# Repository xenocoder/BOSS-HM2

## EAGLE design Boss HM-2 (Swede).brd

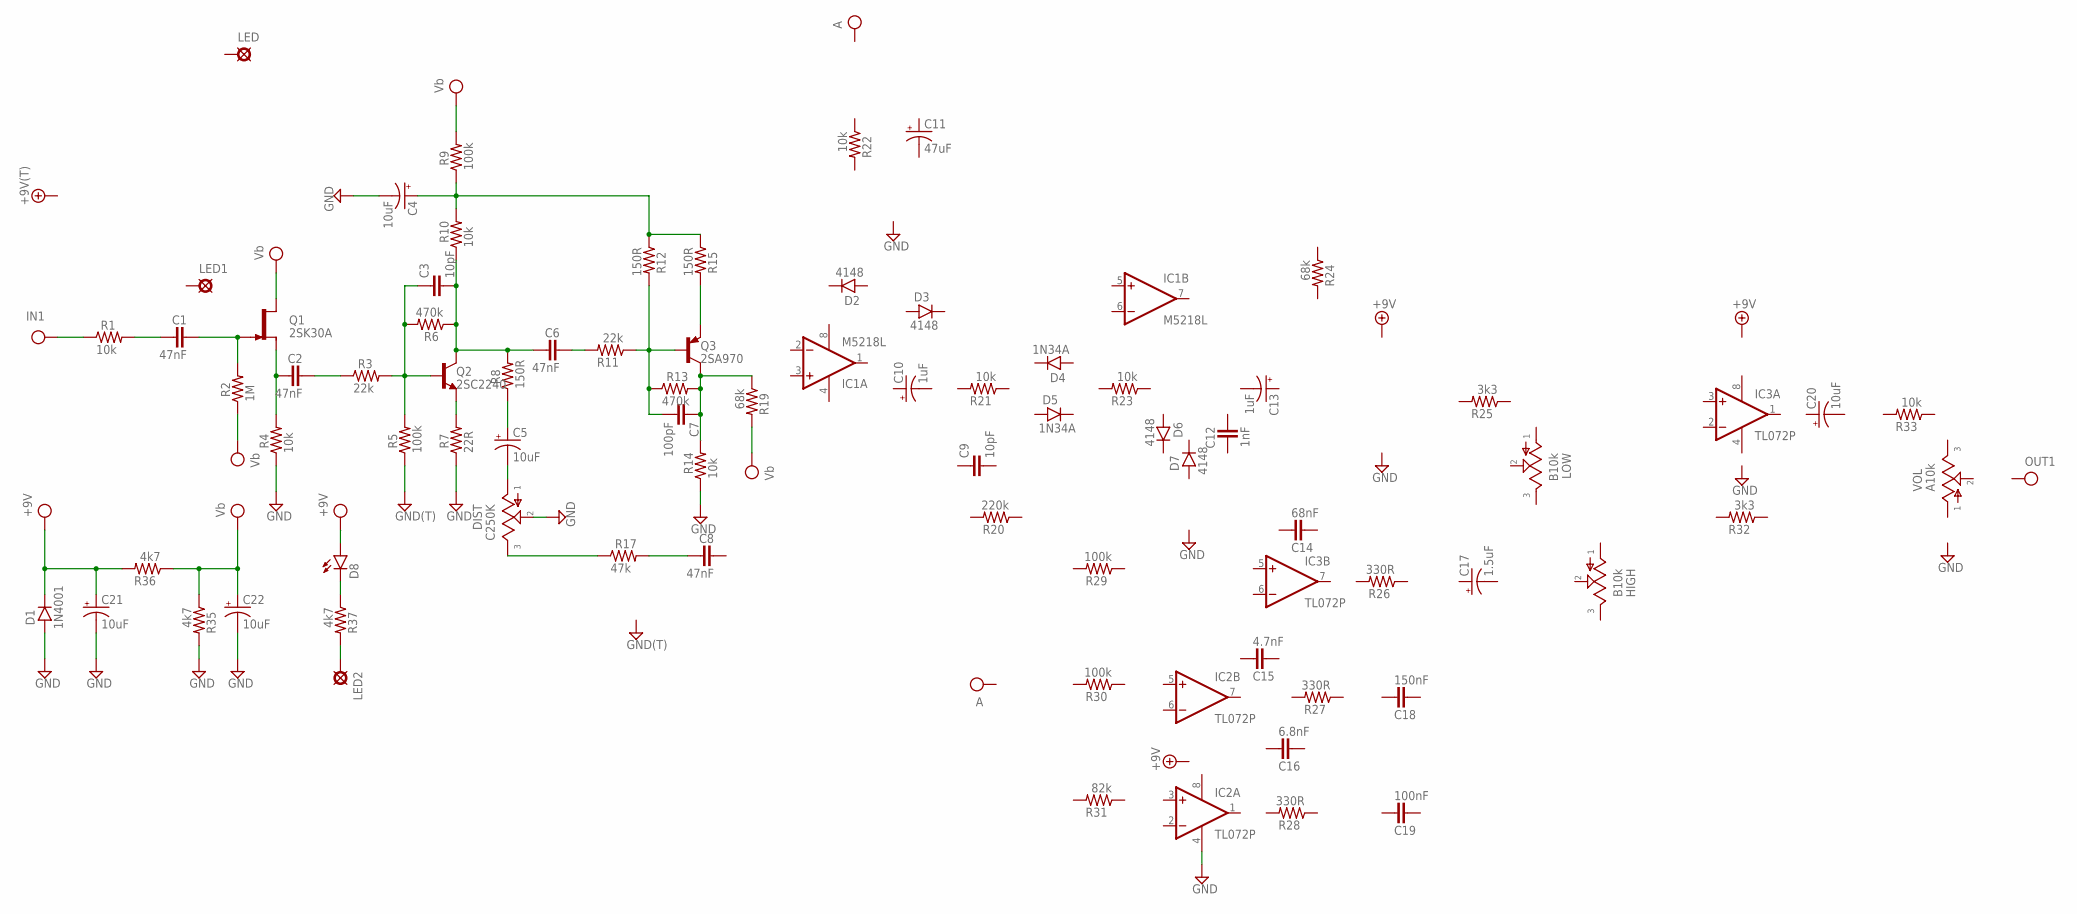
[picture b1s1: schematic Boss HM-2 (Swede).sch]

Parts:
+9V1: +9V(T); SQUARE
C1, C2, C6, C8: 47nF; 072X025
C3, C9: 10pF; 050X030_025
C4, C5, C20, C21, C22: 10uF; 050_020_1
C7: 100pF; 050X030_025
C10, C13: 1uF; 050_020_1
C11: 47uF; 050_020_1
C12: 1nF; 072X025
C14: 68nF; 072X025
C15: 4.7nF; 072X025
C16: 6.8nF; 072X025
C17: 1.5uF; 050_020_1
C18: 150nF; 072X025
C19: 100nF; 072X025
D1: 1N4001; DO35-3
D2, D3, D6, D7: 4148; DO35-3
D4, D5: 1N34A; DO07
D8: LED3MM
DIST: C250K; 16MM_PCB_PADS
GND1, GND2: GND(T); SQUARE
HIGH: B10k; 16MM_PCB_PADS
IC1: M5218L; DIL08
IC2, IC3: TL072P; DIL08
IN1: IN(T); SQUARE
LED, LED1, LED2: PAD; SQUARE
LOW: B10k; 16MM_PCB_PADS
OUT1: OUT(T); SQUARE
Q1: 2SK30A; TO92-
Q2: 2SC2240; TO92-
Q3: 2SA970; TO92-
R1, R4, R10, R14, R21, R22, R23, R33: 10k; R0207/3
R2: 1M; R0207/3
R3, R11: 22k; R0207/3
R5, R9, R29, R30: 100k; R0207/3
R6, R13: 470k; R0207/3
R7: 22R; R0207/3
R8, R12, R15: 150R; R0207/3
R17: 47k; R0207/3
R19, R24: 68k; R0207/3
R20: 220k; R0207/3
R25, R32: 3k3; R0207/3
R26, R27, R28: 330R; R0207/3
R31: 82k; R0207/3
R35, R36, R37: 4k7; R0207/3
VOL: A10k; 16MM_PCB_PADS

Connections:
A: C21.+, C22.+, D1.C, D8.A, Q1.3 (D), R2.1, R9.2, R19.2, R35.1, R36.1, R36.2
GND: C4.-, C21.-, C22.-, D1.A, DIST.2, GND1.1, IC2.4 (V-), R4.1, R5.1, R7.1, R14.1, R35.2
IN: IN1.1, R1.1
unnamed: D8.K (C), R37.1
unnamed: C1.1, R1.2
unnamed: C1.2, Q1.2 (G), R2.2
unnamed: C2.1, Q1.1 (S), R4.2
unnamed: C2.2, R3.1
unnamed: C3.1, Q2.2 (B), R3.2, R5.2, R6.2
unnamed: Q2.3 (E), R7.2
unnamed: C3.2, C6.1, Q2.1 (C), R6.1, R8.2, R10.1
unnamed: C5.+, R8.1
unnamed: C5.-, DIST.1
unnamed: LED2.1, R37.2
unnamed: C4.+, R9.1, R10.2, R12.1, R15.1
unnamed: C6.2, R11.2
unnamed: C7.2, Q3.1 (B), R11.1, R12.2, R13.1
unnamed: C7.1, Q3.2 (C), R13.2, R14.2, R19.1
unnamed: DIST.3, R17.1
unnamed: C8.1, R17.2
unnamed: Q3.3 (E), R15.2
V+: IC1.8 (V+), IC2.8 (V+), IC3.8 (V+)
V-: IC1.4 (V-), IC3.4 (V-)

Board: 2 copper layers, 82 parts (0 on the bottom side), 23 nets, no tracks yet.

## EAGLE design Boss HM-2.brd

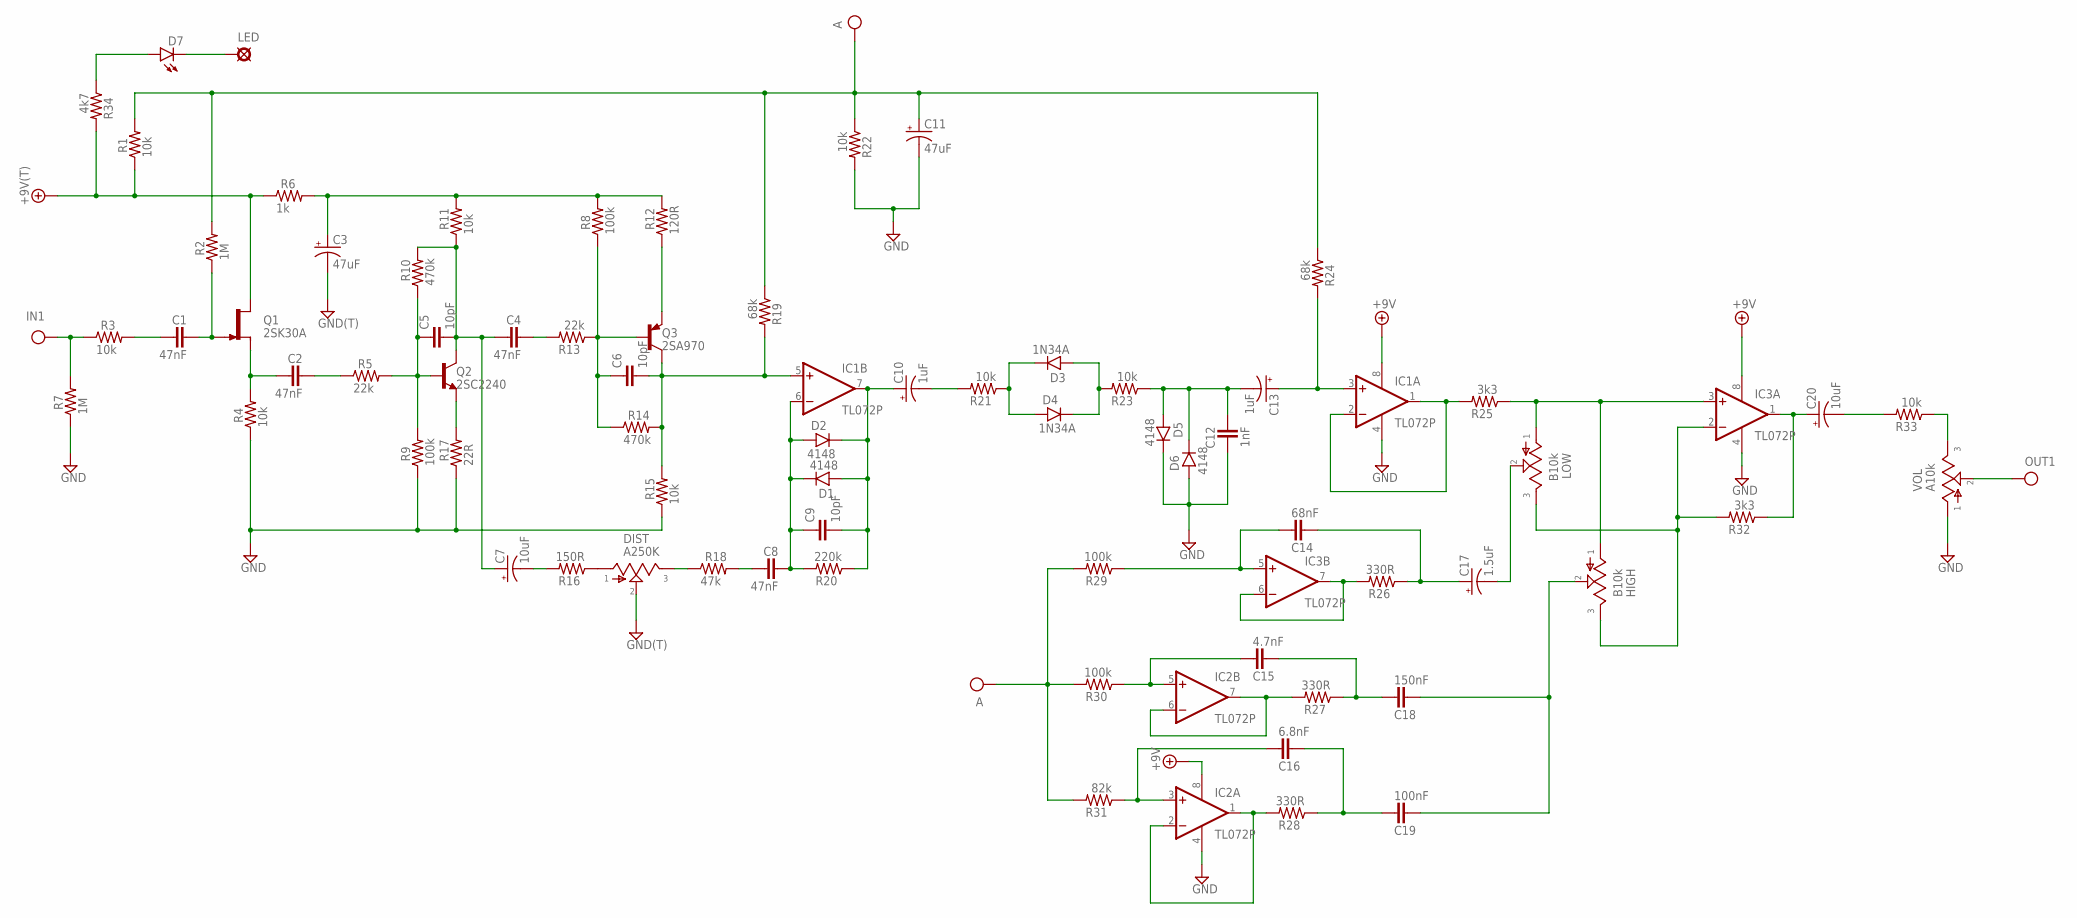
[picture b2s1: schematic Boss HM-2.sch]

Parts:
+9V1: +9V(T); SQUARE
C1, C2, C4, C8: 47nF; 072X025
C3, C11: 47uF; 050_020_1
C5, C6, C9: 10pF; 050X030_025
C7, C20: 10uF; 050_020_1
C10, C13: 1uF; 050_020_1
C12: 1nF; 072X025
C14: 68nF; 072X025
C15: 4.7nF; 072X025
C16: 6.8nF; 072X025
C17: 1.5uF; 050_020_1
C18: 150nF; 072X025
C19: 100nF; 072X025
D1, D2, D5, D6: 4148; DO35-3
D3, D4: 1N34A; DO07
D7: LED3MM
DIST: A250K; 16MM_PCB_PADS
GND1, GND2: GND(T); SQUARE
HIGH: B10k; 16MM_PCB_PADS
IC1, IC2, IC3: TL072P; DIL08
IN1: IN(T); SQUARE
LED: PAD; SQUARE
LOW: B10k; 16MM_PCB_PADS
OUT1: OUT(T); SQUARE
Q1: 2SK30A; TO92-
Q2: 2SC2240; TO92-
Q3: 2SA970; TO92-
R1, R3, R4, R11, R15, R21, R22, R23, R33: 10k; R0207/3
R2, R7: 1M; R0207/3
R5, R13: 22k; R0207/3
R6: 1k; R0207/3
R8, R9, R29, R30: 100k; R0207/3
R10, R14: 470k; R0207/3
R12: 120R; R0207/3
R16: 150R; R0207/3
R17: 22R; R0207/3
R18: 47k; R0207/3
R19, R24: 68k; R0207/3
R20: 220k; R0207/3
R25, R32: 3k3; R0207/3
R26, R27, R28: 330R; R0207/3
R31: 82k; R0207/3
R34: 4k7; R0207/3
VOL: A10k; 16MM_PCB_PADS

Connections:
+9V: +9V1.1, IC1.8 (V+), IC2.8 (V+), IC3.8 (V+), Q1.3 (D), R1.1, R6.1, R34.2
A: C11.+, R1.2, R2.2, R19.1, R22.1, R24.1, R29.2, R30.2, R31.2
GND: C3.-, C11.-, C12.1, D5.C, D6.A, DIST.2, GND1.1, GND2.1, IC1.4 (V-), IC2.4 (V-), IC3.4 (V-), R4.1, R7.1, R9.1, R15.1, R17.1, R22.2, VOL.1
IN: IN1.1, R3.1, R7.2
unnamed: C1.1, R3.2
unnamed: C5.1, Q2.2 (B), R5.2, R9.2, R10.1
unnamed: C1.2, Q1.2 (G), R2.1
unnamed: C3.+, R6.2, R8.2, R11.2, R12.2
unnamed: C2.1, Q1.1 (S), R4.2
unnamed: C2.2, R5.1
unnamed: C4.1, C5.2, C7.+, Q2.1 (C), R10.2, R11.1
unnamed: Q2.3 (E), R17.2
unnamed: C4.2, R13.2
unnamed: C7.-, R16.2
unnamed: C6.1, Q3.1 (B), R8.1, R13.1, R14.1
unnamed: C6.2, IC1.5 (+IN), Q3.2 (C), R14.2, R15.2, R19.2
unnamed: Q3.3 (E), R12.1
unnamed: DIST.1, R16.1
unnamed: DIST.3, R18.1
unnamed: C8.2, C9.1, D1.C, D2.A, IC1.6 (-IN), R20.2
unnamed: C8.1, R18.2
unnamed: D7.A, R34.1
unnamed: C9.2, C10.+, D1.A, D2.C, IC1.7 (OUT), R20.1
unnamed: C10.-, R21.2
unnamed: D3.C, D4.A, R21.1
unnamed: D3.A, D4.C, R23.2
unnamed: C12.2, C13.-, D5.A, D6.C, R23.1
unnamed: C13.+, IC1.3 (+IN), R24.2
unnamed: IC1.1 (OUT), IC1.2 (-IN), R25.2
unnamed: IC2.6 (-IN), IC2.7 (OUT), R27.2
unnamed: C14.2, IC3.5 (+IN), R29.1
unnamed: C15.2, IC2.5 (+IN), R30.1
unnamed: C16.2, IC2.3 (+IN), R31.1
unnamed: D7.K (C), LED.1
unnamed: IC2.1 (OUT), IC2.2 (-IN), R28.2
unnamed: IC3.6 (-IN), IC3.7 (OUT), R26.2
unnamed: C14.1, C17.+, R26.1
unnamed: C15.1, C18.2, R27.1
unnamed: C16.1, C19.2, R28.1
unnamed: C18.1, C19.1, HIGH.2
unnamed: C17.-, LOW.2
unnamed: HIGH.1, IC3.3 (+IN), LOW.1, R25.1
unnamed: HIGH.3, IC3.2 (-IN), LOW.3, R32.2
unnamed: C20.+, IC3.1 (OUT), R32.1
unnamed: C20.-, R33.2
unnamed: R33.1, VOL.3
OUT: OUT1.1, VOL.2

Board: 2 copper layers, 77 parts (0 on the bottom side), 47 nets, no tracks yet.

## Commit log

2015-10-08 First push of files
